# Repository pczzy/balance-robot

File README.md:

# balance-robot
Auto balance 3D printed robot , controll by ESP8266 and driven by stepper motor

## ESP8266 Documentation
http://bbs.espressif.com/viewtopic.php?f=67&t=225

## Arduino Leonardo Summary
* Microcontroller	ATmega32u4
* Operating Voltage	5V
* Input Voltage (recommended)	7-12V
* Input Voltage (limits)	6-20V
* Digital I/O Pins	20
* PWM Channels	7
* Analog Input Channels	12
* DC Current per I/O Pin	40 mA
* DC Current for 3.3V Pin	50 mA
* Flash Memory	32 KB (ATmega32u4) of which 4 KB used by bootloader
* SRAM	2.5 KB (ATmega32u4)
* EEPROM	1 KB (ATmega32u4)
* Clock Speed	16 MHz
* Length	68.6 mm
* Width	53.3 mm
* Weight	20g

## A4988 Documentation
https://www.pololu.com/product/1182

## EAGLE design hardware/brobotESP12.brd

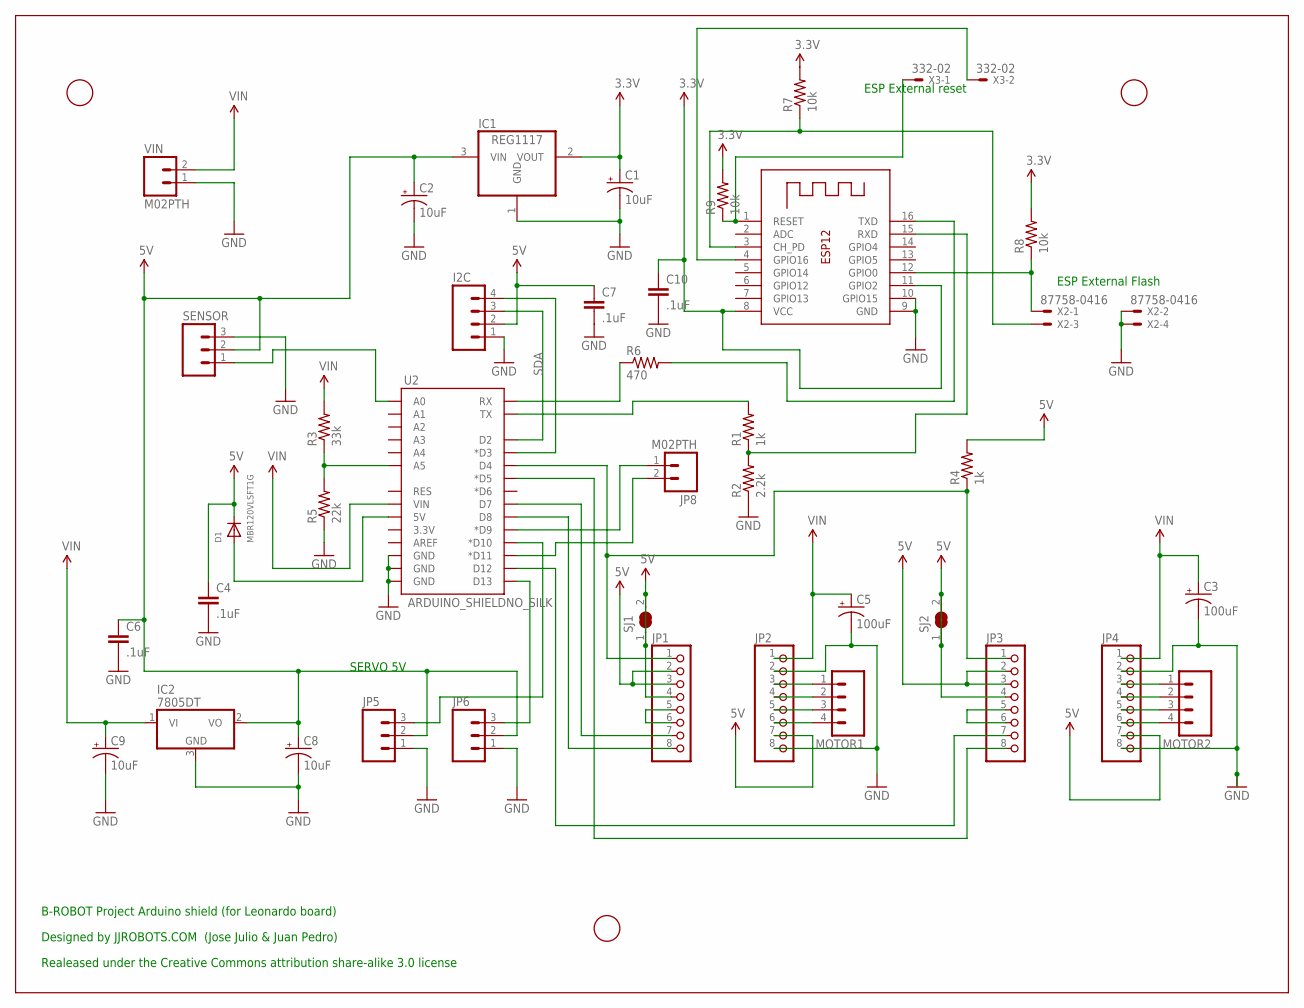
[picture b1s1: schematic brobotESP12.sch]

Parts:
C1, C2, C8, C9: 10uF; EIA3216
C3, C5: 100uF; PANASONIC_D
C4, C6, C7, C10: .1uF; 0402-CAP
D1: MBR120VLSFT1G; SOD-123
I2C: M04PTH; 1X04
IC1: REG1117; SOT223
IC2: 7805DT; TO252
JP1, JP2, JP3, JP4: PINHD-1X8; 1X08
JP5, JP6: M03PTH; 1X03
JP8: M02PTH; 1X02
MOTOR1, MOTOR2: M04PTH; 1X04
R1, R4: 1k; 0805
R2: 2.2k; 0805
R3: 33k; 0805
R5: 22k; 0805
R6: 470; 0805
R7, R8, R9: 10k; 0805
SENSOR: M03PTH; 1X03
SJ1, SJ2: SJW
U2: ARDUINO_SHIELDNO_SILK; DUEMILANOVE_VIAS
U$1, U$2, U$3: FIDUCIAL; FIDUCIAL_1MM
VIN: M02PTH; 1X02
X1: ESP-12
X2: 87758-0416
X3: 332-02

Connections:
3.3V: C1.A (+), C10.1, IC1.2 (VOUT), R7.2, R8.2, R9.2, X1.8 (VCC), X1.11 (GPIO2)
5V: C2.A (+), C4.1, C6.1, C7.1, C8.A (+), D1.C, I2C.2, IC1.3 (VIN), IC2.2 (VO), JP1.2, JP1.3, JP1.4, JP2.7, JP3.2, JP3.3, JP3.4, JP4.7, JP5.2, JP6.2, R4.2, SENSOR.2, SJ1.1, SJ1.2, SJ2.1, SJ2.2
GND: C1.C (-), C2.C (-), C3.-, C4.2, C5.-, C6.2, C7.2, C8.C (-), C9.C (-), C10.2, I2C.1, IC1.1 (GND), IC2.3 (GND), JP2.2, JP2.8, JP4.2, JP4.8, JP5.1, JP6.1, R2.1, R5.1, SENSOR.3, U2.GND@0 (GND), U2.GND@1 (GND), U2.GND@2 (GND), VIN.1, X1.9 (GND), X1.10 (GPIO15), X2.2, X2.4
unnamed: JP2.3, MOTOR1.1
unnamed: JP2.4, MOTOR1.2
unnamed: R6.2, X1.16 (TXD)
unnamed: R1.1, R2.2, X1.15 (RXD)
unnamed: R1.2, U2.TX
unnamed: JP2.5, MOTOR1.3
unnamed: JP2.6, MOTOR1.4
unnamed: JP4.3, MOTOR2.1
unnamed: JP4.4, MOTOR2.2
unnamed: JP4.5, MOTOR2.3
unnamed: JP1.5, JP1.6
unnamed: JP3.5, JP3.6
unnamed: R3.1, R5.2, U2.A5
unnamed: R6.1, U2.RX
unnamed: SENSOR.1, U2.A0
unnamed: JP4.6, MOTOR2.4
unnamed: JP6.3, U2.D13
unnamed: R7.1, X1.3 (CH_PD), X2.3
unnamed: JP5.3, U2.D10 (*D10)
unnamed: R8.1, X1.12 (GPIO0), X2.1
unnamed: JP1.8, U2.D8
unnamed: JP1.7, U2.D7
unnamed: JP1.1, JP3.1, R4.1, U2.D4
unnamed: JP3.8, U2.D5 (*D5)
unnamed: JP3.7, U2.D12
unnamed: D1.A, U2.5V
unnamed: JP8.1, U2.D9 (*D9)
unnamed: JP8.2, U2.D11 (*D11)
unnamed: R9.1, X1.1 (RESET), X3.1
unnamed: X1.4 (GPIO16), X3.2
SCL: I2C.4, U2.D3 (*D3)
SDA: I2C.3, U2.D2
VIN: C3.+, C5.+, C9.A (+), IC2.1 (VI), JP2.1, JP4.1, R3.2, U2.VIN, VIN.2

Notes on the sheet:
SERVO 5V
B-ROBOT Project Arduino shield (for Leonardo board)
Designed by JJROBOTS.COM (Jose Julio & Juan Pedro)
Realeased under the Creative Commons attribution share-alike 3.0 license
ESP External reset
ESP External Flash

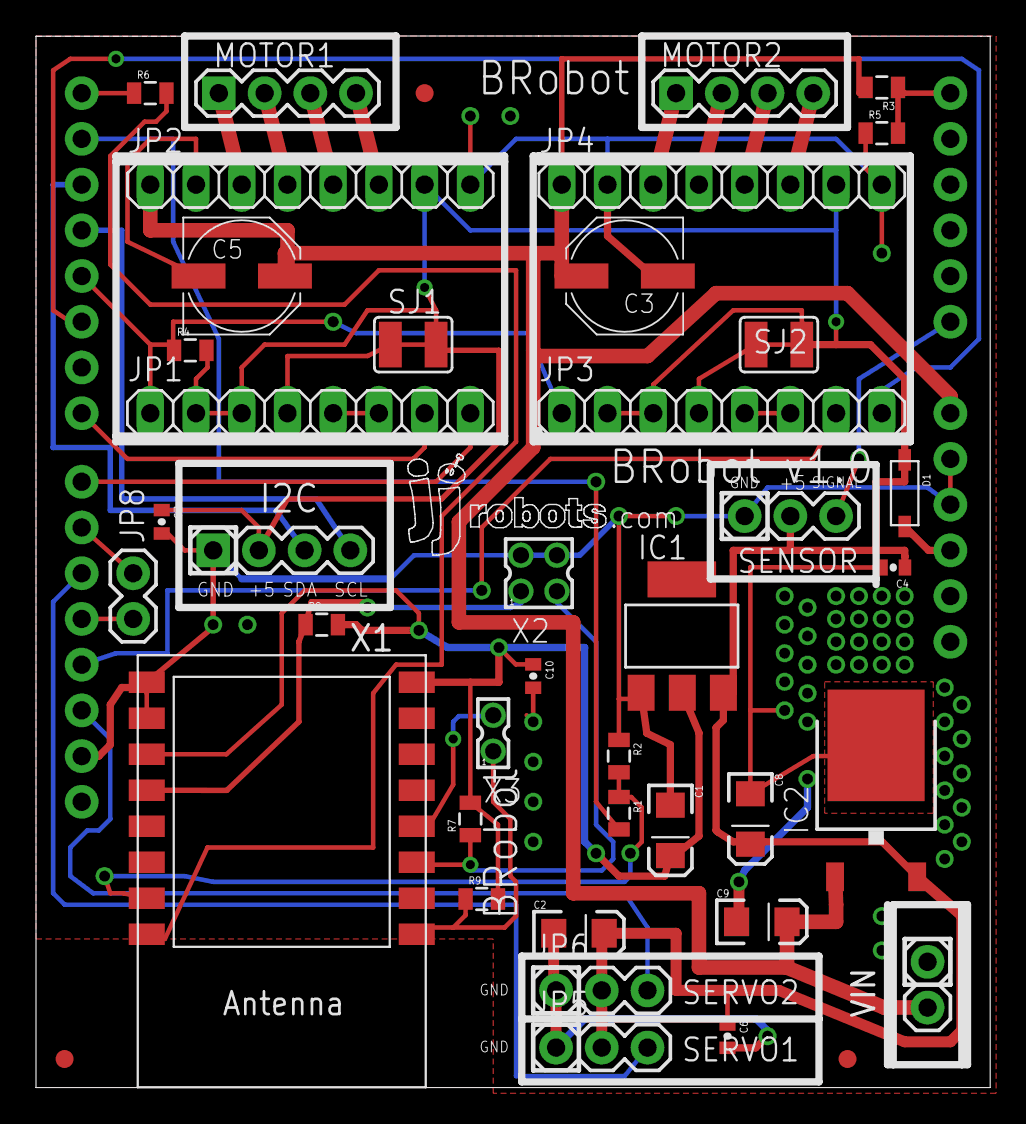
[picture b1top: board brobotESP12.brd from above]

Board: 2 copper layers, 53.0 x 58.4 mm, 43 parts (0 on the bottom side), 36 nets.

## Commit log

2015-12-06 initial commit datasheet adn s3 parts
2015-12-06 add more README.md
2015-12-07 add a4988 data sheet

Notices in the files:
parts and their libraries:
SparkFun-Boards: Licensing: Creative Commons ShareAlike 4.0 International - https://creativecommons.org/licenses/by-sa/4.0
